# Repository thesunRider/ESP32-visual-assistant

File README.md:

# ESP32 AI portable visual-assistant  
### Device Design Requirements:

1. **Audio Playback:**
   - Play audio through a speaker using the Audio BFF amplifier.
   - Include necessary components for driving the speaker.

2. **Battery Charging:**
   - Support rechargeable Li-ion/Li-poly battery integration with efficient charging and power management.
   - Include a charging circuit and IC for managing charging and power distribution to the ESP32-S3.

3. **Connectivity:**
   - Enable Wi-Fi and Bluetooth (including BLE) for app connectivity and efficient power use.

4. **Camera Integration:**
   - Integrate an OV2640 camera module for image and video capture.

5. **Microphone and Control:**
   - Include three tactile buttons for microphone control with LED feedback for status (e.g., mute/unmute).

6. **Enclosure:**
   - Design a compact, 3D-printed enclosure with ports (e.g., USB charging) and provisions for heat dissipation.

# Final Product:

## Technicals
Language: C++ -> Need to create testcases for harware \
Folder Structure :
- Kicad
	- Test (First Prototype)
	- Main (Main Prototype)
- Docs
	- Datasheets
	- Images
- Gerbers

## Technology Used
Listing of Technologies used in the design:
- PMIC - [AXP2101](https://jlcpcb.com/partdetail/x_powersTech-AXP2101/C3036461) 
- Amplifier & Speaker  - [Max98357 Amplifier](https://learn.adafruit.com/adafruit-max98357-i2s-class-d-mono-amp/overview)
- Switches -
- Camera - [OV5640](https://www.waveshare.com/ov5640-camera-board-a.htm)
- Microphone - [Mems Mic](https://learn.adafruit.com/adafruit-i2s-mems-microphone-breakout/)
- Main Unit - [ESP32-S3-WROOM-1-N4](https://www.digikey.de/de/products/detail/espressif-systems/ESP32-S3-WROOM-1-N4/16163950)

## Flowchart

## Energy Charts

While connecting the amplifier , the supply to the amp should go just after the fuel gauge and the over current protection circuit 

| Component | Voltage  | Current  |
|-----------|----------|----------|
| Esp32 S3  | 3v3	 |   650mA       |
| Mic   |     3v3    |      2mA    |
| Amp        | 3v7     |      500mA    |
| Camera | 3v3 , 2v8, 1v5 | 200mA |
| LED 		| 3v3	| 70mA	|
| Extras |3v3 |30mA|

Max current: 1.5A

## Notes
1. Kindly create a seperate page for each new design block (power, camera,mic,...etc) in kicad
2. Kindly Name no connect jumpers as 0ohm resistors and reference as NC
3. BE CAREFUL TO PLACE NC RESISTORS ISOLATED IN FOOTPRINT AS THEY NEED TO BE DESOLDERED OR SOLDERED WITHOUT DISTURBING SURROUNDINGS
4. Refer [Design Considerations](DesignConsideration.md) for specific module requirements
5. Crossrefer pinconnections between footprint and datasheet to check if they are the same.
6. CHECK IF ALL I2S, I2C , SPI AND SDA INTERFACES HAVE PROPER PULLUPS INSTALLED ON SCHEMATIC
7. Breakout a JTAG controller for debugging esp32

## TODO
- [x] Create Kicad Project
- [x] Make BMC and Avail power Rails
- [x] Craete Flowchart
- [x] Create Esp32 Base 
- [x] Create Amp Schematic
- [x] Create Mic Schematic
- [x] Create Camera Schematic - Created a symbol in Kicad for testing (proceeding with it - need reverse engineer testing)
- [x] Add switch Schematic
- [x] Link Components to PCB 
- [x] Test Cases for Hardware

Project Finished Rev2 Board created with superior perfomance

## Reference
Kindly put circuit reference here
1. USB from here: https://github.com/jenschr/USB-C-Connectors
2. PMIC Reference Design https://oshwhub.com/mondraker/axp2101_2023-11-18_20-15-19

## Components Sourcing
Adafruit OV5640 Camera Breakout
-  Breakout Board uses FD5640 500W Camera sensor
-  Available in bluk from Aliexpress
- Switch: K2-1114SA-A4SW-06, https://jlcpcb.com/partdetail/OmronElectronics-B3S1000/C2733655 Check pin configs
- Switch: K2-1114SA-A4SW-06, https://jlcpcb.com/partdetail/OmronElectronics-B3S1000/C2733655
- Speakers , https://www.lcsc.com/product-detail/Speakers_INGHAi-GSPK151035PN-8R0-5W-L35-1-25T_C530539.html
- Tactile Switches https://de.aliexpress.com/item/32912259140.html?gatewayAdapt=glo2deu

AXP2101 Component
- Inductor   3.1A 1uH ±20% 0806 Power Inductors ROHS
  https://www.lcsc.com/product-detail/Power-Inductors_Chilisin-Elec-HEI201610K-1R0M-Q8DG_C329576.html

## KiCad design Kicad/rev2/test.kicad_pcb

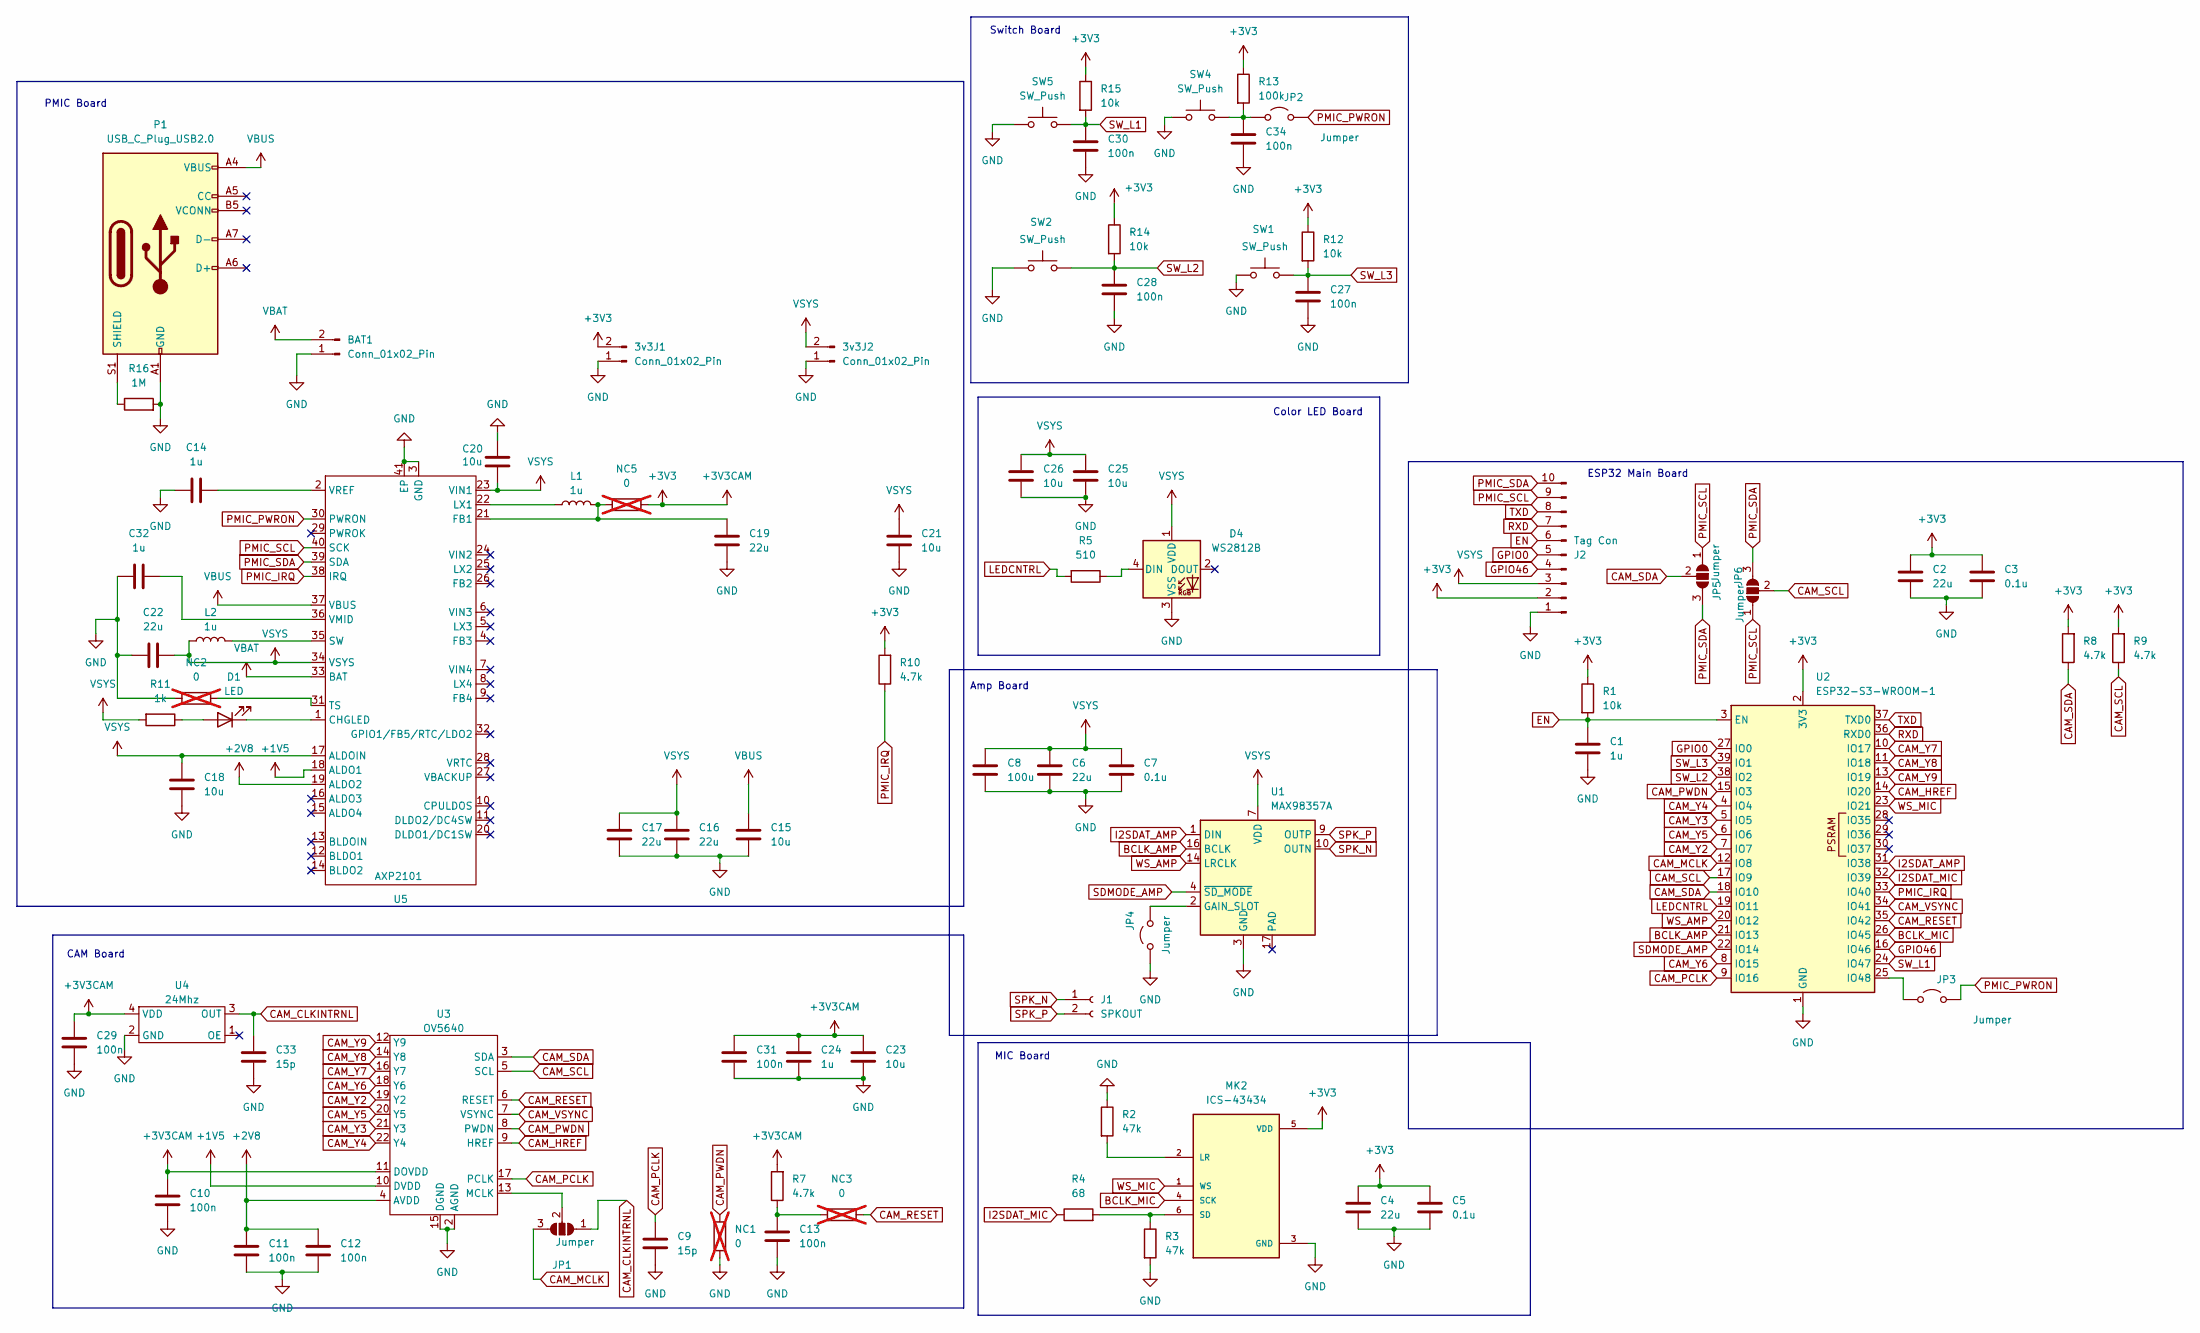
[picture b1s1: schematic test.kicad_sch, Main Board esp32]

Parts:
3v3J1, 3v3J2: Conn_01x02_Pin; SMD_CONNECTOR_PAD
BAT1: Conn_01x02_Pin; SMD_CONNECTOR_PAD
C1, C14, C24, C32: 1u; C_0603_1608Metric
C2, C4, C6, C16, C17, C19, C22: 22u; C_0603_1608Metric_Pad1.08x0.95mm_HandSolder
C3, C5, C7: 0.1u; C_0603_1608Metric_Pad1.08x0.95mm_HandSolder
C8: 100u; C_0805_2012Metric
C9, C33: 15p; C_0402_1005Metric
C10, C11, C12, C13, C27, C28, C29, C30, C31, C34: 100n; C_0402_1005Metric; Mfr. # CL05B104KO5NNNC; LCSC Part # C1525
C15, C18, C20, C21, C25, C26: 10u; C_0603_1608Metric_Pad1.08x0.95mm_HandSolder
C23: 10u; C_0603_1608Metric
D1: LED; LED_0402_1005Metric
D4: WS2812B; LED_WS2812B_PLCC4_5.0x5.0mm_P3.2mm; Mfr Part XL-5050RGBC-WS2812B-S; LCSC Part C22461793
J1: SPKOUT; SMD_CONNECTOR_PAD
J2: Tag Con; TAG-CONNECT_TC2050-IDC
JP1, JP5, JP6: Jumper; SolderJumper-3_P1.3mm_Open_RoundedPad1.0x1.5mm
JP2, JP3, JP4: Jumper; SolderJumper-2_P1.3mm_Open_TrianglePad1.0x1.5mm
L1, L2: 1u; L_0805_2012Metric_Pad1.05x1.20mm_HandSolder; Mfr Part AHW2012F-1R0KTF; LCSC Part C6364721
MK2: ICS-43434; InvenSense_ICS-43434-6_3.5x2.65mm; Mfr Part ICS-43434; LCSC Part C5656610
NC1, NC2, NC3, NC5: 0; R_1206_3216Metric; not fitted
P1: USB_C_Plug_USB2.0; USB_C_Receptacle_HRO_TYPE-C-31-M-12; Mfr Part TYPE-C-31-M-14; LCSC Part C223907
R1: 10k; R_0603_1608Metric
R2, R3: 47k; R_0603_1608Metric_Pad0.98x0.95mm_HandSolder
R4: 68; R_0603_1608Metric_Pad0.98x0.95mm_HandSolder
R5: 510; R_0603_1608Metric_Pad0.98x0.95mm_HandSolder
R7, R8, R9, R10: 4.7k; R_0603_1608Metric_Pad0.98x0.95mm_HandSolder
R11: 1k; R_0603_1608Metric_Pad0.98x0.95mm_HandSolder
R12, R14, R15: 10k; R_0603_1608Metric_Pad0.98x0.95mm_HandSolder
R13: 100k; R_0603_1608Metric_Pad0.98x0.95mm_HandSolder
R16: 1M; R_0603_1608Metric_Pad0.98x0.95mm_HandSolder
SW1, SW2: SW_Push; SW2_1825027-C_TEC; Mfr Part 1825027-8; LCSC Part C266196
SW4: SW_Push; K2-1114SA-A4SW-06; Mfr Part K2-1114SA-A4SW-06; LCSC Part C136662
SW5: SW_Push; SW_SPST_B3S-1000; Mfr Part B3S-1000; LCSC Part C2733655
U1: MAX98357A; 21-0136I_T1633-4_MXM-M; Mfr Part MAX98357AETE+T; LCSC Part C910544
U2: ESP32-S3-WROOM-1
U3: OV5640; TE_2-1734839-4_1x24-1MP_P0.5mm_Horizontal; Mfr Part AFC01-S24FCA-00; LCSC Part C262669
U4: 24Mhz; YSO110TR; Mfr Part OT252024MJBA4SL; LCSC Part C669072
U5: AXP2101; QFN-40-1EP_5x5mm_P0.4mm_EP3.6x3.6mm; Mfr Part AXP2101; LCSC Part C3036461

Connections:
+1V5: U3.10 (DVDD), U5.18 (ALDO1)
+2V8: C11.1, C12.1, U3.4 (AVDD), U5.19 (ALDO2)
+3V3: 3v3J1.2, C2.1, C3.1, C4.1, C5.1, C10.1, C23.2, C24.2, C29.1, C31.1, J2.2, MK2.5 (VDD), NC5.2, R1.1, R7.2, R8.2, R9.2, R10.2, R12.1, R13.1, R14.1, R15.1, U2.2 (3V3), U3.11 (DOVDD), U4.4 (VDD)
BCLK_AMP: U1.16 (BCLK), U2.21 (IO13)
BCLK_MIC: MK2.4 (SCK), U2.26 (IO45)
CAM_CLKINTRNL: C33.1, JP1.1 (A), U4.3 (OUT)
CAM_HREF: U2.14 (IO20), U3.9 (HREF)
CAM_MCLK: JP1.3 (B), U2.12 (IO8)
CAM_PCLK: C9.1, U2.9 (IO16), U3.17 (PCLK)
CAM_PWDN: NC1.1, U2.15 (IO3), U3.8 (PWDN)
CAM_RESET: NC3.2, U2.35 (IO42), U3.6 (RESET)
CAM_SCL: JP5.2 (C), R9.1, U2.17 (IO9), U3.5 (SCL)
CAM_SDA: JP6.2 (C), R8.1, U2.18 (IO10), U3.3 (SDA)
CAM_VSYNC: U2.34 (IO41), U3.7 (VSYNC)
CAM_Y2: U2.7 (IO7), U3.19 (Y2)
CAM_Y3: U2.5 (IO5), U3.21 (Y3)
CAM_Y4: U2.4 (IO4), U3.22 (Y4)
CAM_Y5: U2.6 (IO6), U3.20 (Y5)
CAM_Y6: U2.8 (IO15), U3.18 (Y6)
CAM_Y7: U2.10 (IO17), U3.16 (Y7)
CAM_Y8: U2.11 (IO18), U3.14 (Y8)
CAM_Y9: U2.13 (IO19), U3.12 (Y9)
EN: C1.1, J2.6, R1.2, U2.3 (EN)
GND: 3v3J1.1, 3v3J2.1, BAT1.1, C1.2, C2.2, C3.2, C4.2, C5.2, C6.2, C7.2, C8.2, C9.2, C10.2, C11.2, C12.2, C13.2, C14.1, C15.1, C16.1, C17.1, C18.1, C19.1, C20.2, C21.1, C22.2, C23.1, C24.1, C25.1, C26.1, C27.2, C28.2, C29.2, C30.2, C31.2, C32.1, C33.2, C34.2, D4.3 (VSS), J2.1, JP4.1 (A), MK2.3 (GND), NC1.2, NC2.1, P1.A1 (GND), P1.A12 (GND), P1.B1 (GND), P1.B12 (GND), R2.1, R3.2, R16.2, SW1.1, SW2.1, SW4.1, SW5.1, U1.3 (GND), U1.11 (GND), U1.15 (GND), U2.1 (GND), U2.40 (GND), U2.41 (GND), U3.2 (AGND), U3.15 (DGND), U4.2 (GND), U5.3 (GND), U5.41 (EP)
GPIO0: J2.5, U2.27 (IO0)
GPIO46: J2.4, U2.16 (IO46)
I2SDAT_AMP: U1.1 (DIN), U2.31 (IO38)
I2SDAT_MIC: R4.1, U2.32 (IO39)
LEDCNTRL: R5.2, U2.19 (IO11)
unnamed: C13.1, NC3.1, R7.1
unnamed: D1.2 (A), R11.1
unnamed: D1.1 (K), U5.1 (CHGLED)
unnamed: D4.4 (DIN), R5.1
unnamed: JP1.2 (C), U3.13 (MCLK)
unnamed: C34.1, JP2.1 (A), R13.2, SW4.2
unnamed: JP3.1 (A), U2.25 (IO48)
unnamed: JP4.2 (B), U1.2 (GAIN_SLOT)
unnamed: MK2.2 (LR), R2.2
unnamed: MK2.6 (SD), R3.1, R4.2
unnamed: P1.S1 (SHIELD), R16.1
unnamed: C19.2, L1.2, NC5.1, U5.21 (FB1)
unnamed: L1.1, U5.22 (LX1)
unnamed: L2.2, U5.35 (SW)
unnamed: NC2.2, U5.31 (TS)
unnamed: C32.2, U5.36 (VMID)
unnamed: C14.2, U5.2 (VREF)
PMIC_IRQ: R10.1, U2.33 (IO40), U5.38 (IRQ)
PMIC_PWRON: JP2.2 (B), JP3.2 (B), U5.30 (PWRON)
PMIC_SCL: J2.9, JP5.1 (A), JP6.1 (A), U5.40 (SCK)
PMIC_SDA: J2.10, JP5.3 (B), JP6.3 (B), U5.39 (SDA)
RXD: J2.7, U2.36 (RXD0)
SDMODE_AMP: U1.4 (~SD_MODE), U2.22 (IO14)
SPK_N: J1.1, U1.10 (OUTN)
SPK_P: J1.2, U1.9 (OUTP)
SW_L1: C30.1, R15.2, SW5.2, U2.24 (IO47)
SW_L2: C28.1, R14.2, SW2.2, U2.38 (IO2)
SW_L3: C27.1, R12.2, SW1.2, U2.39 (IO1)
TXD: J2.8, U2.37 (TXD0)
VBAT: BAT1.2, U5.33 (BAT)
VBUS: C15.2, P1.A4 (VBUS), P1.A9 (VBUS), P1.B4 (VBUS), P1.B9 (VBUS), U5.37 (VBUS)
VSYS: 3v3J2.2, C6.1, C7.1, C8.1, C16.2, C17.2, C18.2, C20.1, C21.2, C22.1, C25.2, C26.2, D4.1 (VDD), J2.3, L2.1, R11.2, U1.7 (VDD), U1.8 (VDD), U5.17 (ALDOIN), U5.23 (VIN1), U5.34 (VSYS)
WS_AMP: U1.14 (LRCLK), U2.20 (IO12)
WS_MIC: MK2.1 (WS), U2.23 (IO21)

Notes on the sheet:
ESP32 Main Board
PMIC Board
Color LED Board
Switch Board
Amp Board
MIC Board
CAM Board

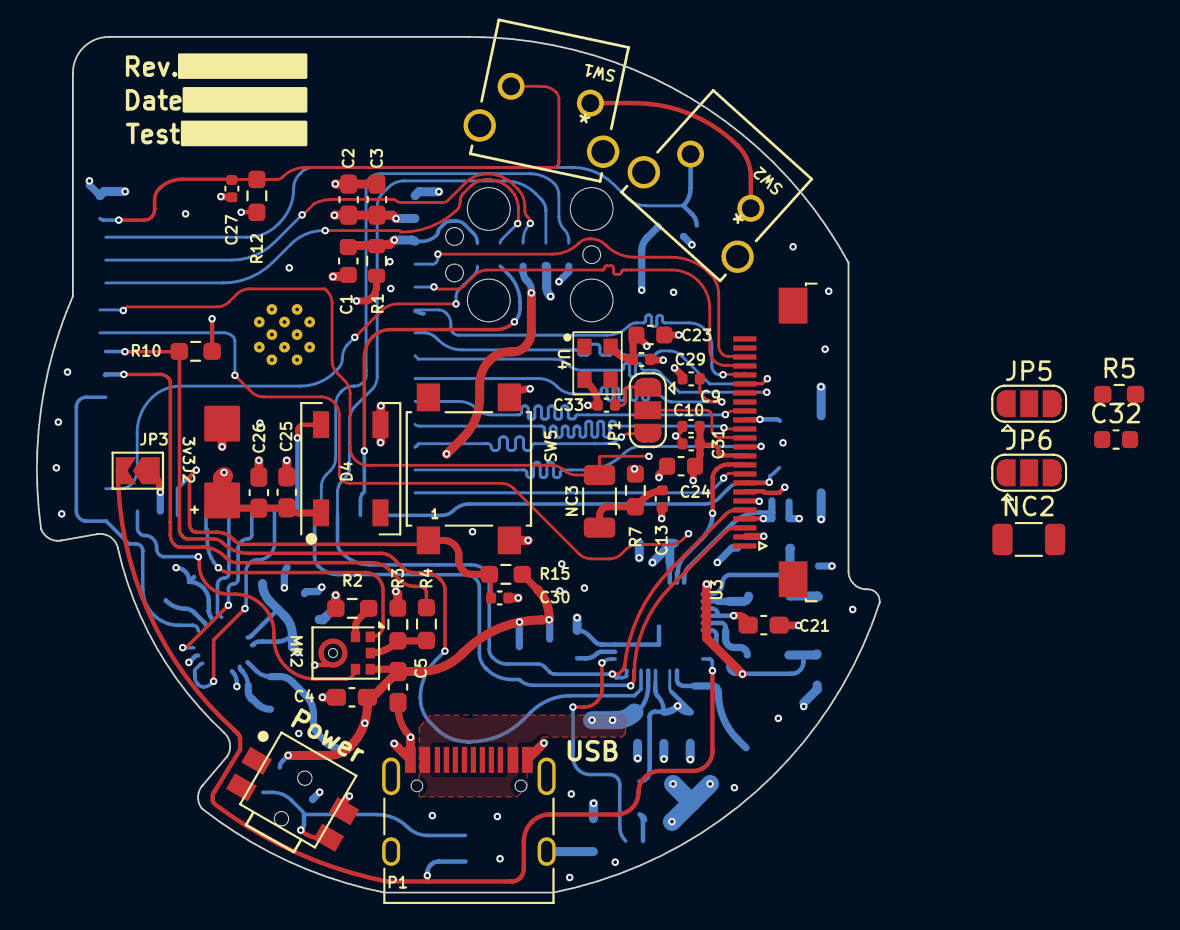
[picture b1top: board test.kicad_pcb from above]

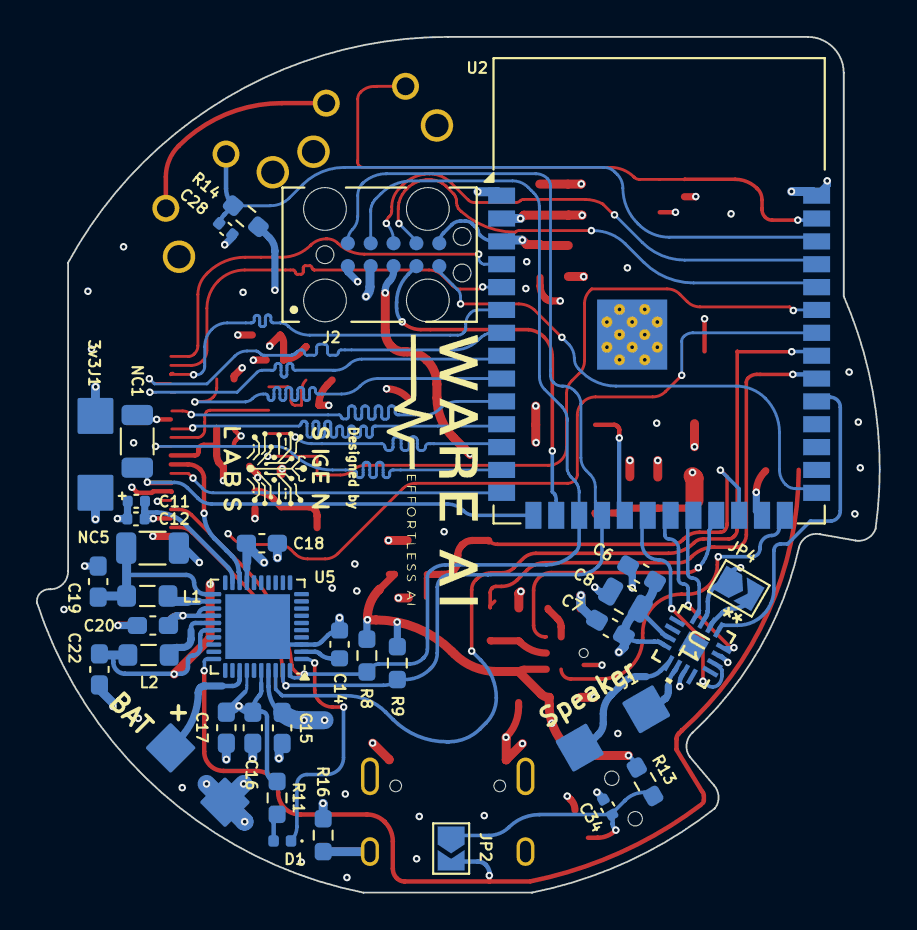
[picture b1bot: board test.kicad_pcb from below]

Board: 4 copper layers, 46.8 x 47.5 mm, 79 parts (35 on the bottom side), 63 nets.

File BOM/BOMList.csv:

null,Designator,Value,Footprint,Description,LCSC Part #,Mfr Part,Quantity,,
1,"C10, C11, C12, C13, C27, C28, C29, C30, C31, C34",100n,C_0402_1005Metric,Unpolarized capacitor,C1525,CL05B104KO5NNNC,10,,16V 100nF X7R ±10% 0402 Multilayer Ceramic Capacitors MLCC - SMD/SMT ROHS
2,"C2, C4, C6, C16, C17, C19, C22",22u,C_0603_1608Metric_Pad1.08x0.95mm_HandSolder,Unpolarized capacitor,C59461,CL10A226MQ8NRNC,7,,6.3V 22uF X5R ±20% 0603 Multilayer Ceramic Capacitors MLCC - SMD/SMT ROHS
3,"C15, C18, C20, C21,C23, C25, C26,",10u,C_0603_1608Metric_Pad1.08x0.95mm_HandSolder,Unpolarized capacitor,C19702,CL10A106KP8NNNC,6,,10V 10uF X5R ±10% 0603 Multilayer Ceramic Capacitors MLCC - SMD/SMT ROHS
4,"C3, C5, C7",0.1u,C_0603_1608Metric_Pad1.08x0.95mm_HandSolder,Unpolarized capacitor,C14663,CC0603KRX7R9BB104,3,,50V 100nF X7R ±10% 0603 Multilayer Ceramic Capacitors MLCC - SMD/SMT ROHS
5,"C9, C33",15p,C_0402_1005Metric,Unpolarized capacitor,C1548,0402CG150J500NT,2,,50V 15pF C0G ±5% 0402 Multilayer Ceramic Capacitors MLCC - SMD/SMT ROHS
6,"C1, C14, C24",1u,C_0603_1608Metric,Unpolarized capacitor,C15849,CL10A105KB8NNNC,3,,50V 1uF X5R ±10% 0603 Multilayer Ceramic Capacitors MLCC - SMD/SMT ROHS
7,C8,100u,C_0603_1608Metric_Pad1.08x0.95mm_HandSolder,Unpolarized capacitor,C141660,GRM21BR60J107ME15L,1,,6.3V 100uF X5R ±20% 0805 Multilayer Ceramic Capacitors MLCC - SMD/SMT ROHS
9,"R1, R8, R9, R12, R13, R14, R15",10k,R_0603_1608Metric_Pad0.98x0.95mm_HandSolder,Resistor,C25804,0603WAF1002T5E,7,,100mW Thick Film Resistors 75V ±100ppm/? ±1% 10k? 0603 Chip Resistor - Surface Mount ROHS
10,"R2, R3",47k,R_0603_1608Metric_Pad0.98x0.95mm_HandSolder,Resistor,C25819,0603WAF4702T5E,2,,100mW Thick Film Resistors 75V ±100ppm/? ±1% 47k? 0603 Chip Resistor - Surface Mount ROHS
11,"R7, R10",4.7k,R_0603_1608Metric_Pad0.98x0.95mm_HandSolder,Resistor,C23162,0603WAF4701T5E,2,,100mW Thick Film Resistors 75V ±100ppm/? ±1% 4.7k? 0603 Chip Resistor - Surface Mount ROHS
12,R4,68,R_0603_1608Metric_Pad0.98x0.95mm_HandSolder,Resistor,C27592,0603WAF680JT5E,1,,100mW Thick Film Resistors 75V ±100ppm/? ±1% 68? 0603 Chip Resistor - Surface Mount ROHS
13,R11,1k,R_0603_1608Metric_Pad0.98x0.95mm_HandSolder,Resistor,C21190,0603WAF1001T5E,1,,100mW Thick Film Resistors 75V ±100ppm/? ±1% 1k? 0603 Chip Resistor - Surface Mount ROHS
14,R16,1M,R_0603_1608Metric_Pad0.98x0.95mm_HandSolder,Resistor,C22935,0603WAF1004T5E,1,,100mW Thick Film Resistors 75V ±100ppm/? ±1% 1M? 0603 Chip Resistor - Surface Mount ROHS
15,"L1, L2",1u,L_0805_2012Metric_Pad1.05x1.20mm_HandSolder,Inductor,C6364721,AHW2012F-1R0KTF,2,,430mA 1uH ±10% 1? 0805 Inductors (SMD) ROHS
16,D1,LED,LED_0402_1005Metric,Light emitting diode,C965793,XL-1005UGC,1,,25mA 249mcd Colorless transparent lens -30?~+85? Positive Stick 516nm~531nm Emerald 120° 80mW 3V 0402 LED Indication - Discrete ROHS
17,D4,WS2812B,LED_WS2812B_PLCC4_5.0x5.0mm_P3.2mm,RGB LED with integrated controller,C22461793,XL-5050RGBC-WS2812B-S,1,,"SMD-4P,5x5mm RGB LEDs(Built-in IC) ROHS"
18,U1,MAX98357A,TQFN-16-1EP_3x3mm_P0.5mm_EP1.23x1.23mm,Monaural 3.2Wx2@4Î© BGA-9(1.3x1.3) Audio Amplifiers ROHS,C2682619,MAX98357AEWL+T,1,,
19,U2,ESP32-S3-WROOM-1,ESP32-S3-WROOM-1,"RF Module, ESP32-S3 SoC, Wi-Fi 802.11b/g/n, Bluetooth, BLE, 32-bit, 3.3V, onboard antenna, SMD",C2913205,,1,,
20,U3,OV5640,TE_2-1734839-4_1x24-1MP_P0.5mm_Horizontal,"Flip type 24P Bottom Contact Horizontal attachment 0.5mm SMD,P=0.5mm,Surface Mountï¼Right Angle FFC, FPC (Flat Flexible) Connector Assemblies ROHS",C262669,AFC01-S24FCA-00,1,,
21,U4,24Mhz,YSO110TR,1.8V~3.3V Â±10ppm 4mA Â±20ppm CMOS 24MHz SMD2520-4P Crystal Oscillators ROHS,C669072,OT252024MJBA4SL,1,,
22,U5,AXP2101,QFN-40-1EP_5x5mm_P0.4mm_EP3.6x3.6mm,QFN-40-EP(5x5) Power Management - Specialized ROHS,C3036461,AXP2101,1,,
23,"SW1, SW2",SW_Push,SW2_1825027-C_TEC,3.25mm Round Button 50mA Bend-in SPST 160gf 24V Plugin Tactile Switches ROHS,C266196,1825027-8,2,,
24,SW4,SW_Push,K2-1114SA-A4SW-06,3.5mm 1.65mm Rectangle button 50mA Horizontal attachment 4.8mm SPST 100000 Times 250gf 12V SMD Tactile Switches ROHS,C136662,K2-1114SA-A4SW-06,1,,
25,SW5,SW_Push,SW_SPST_B3S-1000,Tactile Switches ROHS,C2733655,B3S-1000,1,,
27,"JP2, JP3, JP4",Jumper,SolderJumper-2_P1.3mm_Open_TrianglePad1.0x1.5mm,"Jumper, 2-pole, open",,,3,,
28,"NC1, NC3, NC5",0,R_1206_3216Metric,Resistor,,,3,,
29,MK2,ICS-43434,InvenSense_ICS-43434-6_3.5x2.65mm,Omni-directional 64dB MEMS Microphones ROHS,C5656610,ICS-43434,1,,
31,P1,USB_C_Plug_USB2.0,USB_C_Receptacle_HRO_TYPE-C-31-M-12,USB 2.0-only Type-C Plug connector,C2982555,TYPE-C-31-M-14,1,,

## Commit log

2024-12-09 Added Readme
2024-12-09 Folderstructure
2024-12-09 Added Readme defs
2024-12-09 Added more readme
2024-12-09 Created Kicad project
2024-12-10 created folder structures
2024-12-10 Added design considerations
2024-12-10 Added extras
2024-12-10 Added esp32 consideration
2024-12-10 Implemented Esp32 circuits
2024-12-10 Implemented Amplifier
2024-12-14 Update README.md
    Sourcing Heading Added
2024-12-14 Researched OV5640
2024-12-15 Implemented ov5640
2024-12-15 Modified pinouts
2024-12-15 Started PMIC Integration
2024-12-15 README PMIC Integration
2024-12-15 Update DesignConsideration.md
    ESD
2024-12-16 Schematic finished
2024-12-16 Added Battery plugin in schematic
2024-12-17 Started PCB Layout designs
2024-12-17 Placed components on PCB
2024-12-17 Update README.md
    Inductor added
2024-12-18 updated schematic symbols
2024-12-23 v0.1
2024-12-24 Added Clock for Camera
2024-12-24 3d Model Casing and PCB Added
2024-12-24 Floorplanning done
2024-12-24 Started PCB routing
2024-12-26 Updated schematics
2024-12-26 Updated PCB floor
2024-12-26 PCB updated
2024-12-26 Checked schematic and PCB
2024-12-29 Rerouted pin connections on esp32
2024-12-29 Connected a missing piece
2024-12-29 DRC Corrections done on schematic
2025-01-02 50% Routing Done
2025-01-02 Routing
2025-01-04 Mouting hole Added
2025-01-06 ROUTED MORE
2025-01-06 ROUTED camera
2025-01-06 Routing 80% Done
2025-01-06 Routing 95% done
2025-01-07 Exposed i2c pads of camera and pmic too and finished routing
2025-01-07 Zones created Finished Routing
2025-01-07 Finished layouts and offsetting
2025-01-07 Completed
2025-01-07 Routing completed
2025-01-08 Mounting Hole added
2025-01-09 Optimizing for DFM still pending
2025-01-09 DFM completed Logo added
2025-01-09 CPL file updated as Per JLCPcb requirements
2025-01-09 Via Size update 0.2 mm drill 0.4 mm diameter
2025-01-09 Updated Via Size
2025-01-14 Redone footprint of Component Crystal
2025-01-14 Updated Orientations
2025-01-16 JLCPCB Invoice 15-01-25
2025-01-26 Finished REV1 Design and created pcb
2025-01-26 Unit Tested build
2025-01-26 Finished Rev2 Schematic
2025-01-26 Finished Project TEADME
